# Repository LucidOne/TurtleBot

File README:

I Heart Engineering Documentation and Tools for the TurtleBot

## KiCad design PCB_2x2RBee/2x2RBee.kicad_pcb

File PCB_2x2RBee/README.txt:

2x2RBee
GPIO Control for the Raspberry Pi with XBee Shield included

BOM
Qty.	Item					Digikey P. No.		Manufacturer		Manufacturer P. No.	url
----------------------------------------------------------------------------------------------------------------------------------	

5	CONN TERM BLOCK 2.54MM 2POS PCB		ED10561-ND		On Shore Technology Inc	OSTVN02A150		http://www.on-shore.com/sites/default/files/manuals/ostvnxxa150.pdf

1	CONN JACK POWER 2.1MM PCB		CP-102A-ND		CUI Inc			PJ-102A			http://www.cui.com/Product/Resource/DigiKeyPDF/PJ-102A.pdf

1	CONN HEADR FMALE 26POS .1" DL AU	S9198-ND	Sullins Connector Solutions	SFH11-PBPC-D13-ST-BK	http://media.digikey.com/pdf/Data%20Sheets/Sullins%20PDFs/SFH11-PxxC-Dxx-ST-xx%2011160-C.pdf

1	CONN RCPT REV MICRO USB TYPE B		609-4048-1-ND		FCI			10103592-0001LF		http://portal.fciconnect.com/Comergent//fci/drawing/10103592.pdf

2	RELAY GENERAL PURPOSE SPST 3A 5V	PCN-105D3MHZ 000-ND 	TE Connectivity		PCN-105D3MHZ,000	http://www.te.com/commerce/DocumentDelivery/DDEController?Action=srchrtrv&DocNm=1461491&DocType=Customer+Drawing&DocLang=English

1	PHOTOCOUPLER DUAL 6N136 8-DIP		TLP2531F-ND		Toshiba			TLP2531(F)		http://www.semicon.toshiba.co.jp/info/docget.jsp?type=datasheet&lang=en&pid=TLP2530

2	IC SGL SCHMT-TRIG INVERT SC70-5		296-11608-1-ND		Texas Instruments	SN74LVC1G14DCKR		http://www.ti.com/lit/ds/symlink/sn74lvc1g14.pdf

2	IC REG LDO 5V .15A SOT23-5		296-20717-1-ND		Texas Instruments	LP2985-50DBVT		http://www.ti.com/lit/ds/symlink/lp2985-18.pdf

5	1K Resistor				P1.00KCTR-ND		Panasonic - ECG		ERJ-6ENF1001V	http://industrial.panasonic.com/www-data/pdf/AOA0000/AOA0000PE3.pdf

2 	RES 680 OHM 1/8W 1% 0805 SMD		311-680CRTR-ND		Yageo			RC0805FR-07680RL	http://www.yageo.com/documents/recent/PYu-RC0805_51_RoHS_L_4.pdf	

1	SWITCH SLIDE SPDT 30V.2A PC MNT		EG1903-ND		E-Switch			EG1218		http://spec.e-switch.com/P-J/P040040c.pdf

3	LED_0805				754-1131-2-ND		Kingbright Corp		APT2012SGC	http://www.us.kingbright.com/images/catalog/SPEC/APT2012SGC.pdf

1	FUSE PTC RESET 2.0A 6V 1206 SMD			F4155CT-ND		Littelfuse Inc		1206L200PR		http://www.littelfuse.com/~/media/Files/Littelfuse/Technical%20Resources/Documents/Data%20Sheets/Littelfuse_PTC_1206L.pdf

1	DIODE SCHOTTKY 40V 2A 1206			478-7806-1-ND		AVX Corporation		SD1206S040S2R0		http://www.avx.com/docs/Catalogs/schottky.pdf

2 	CONN SOCKET 10POS 2MM VERT T/H		3M9405-ND		3M		950510-6102-AR		http://multimedia.3m.com/mws/mediawebserver?66666UuZjcFSLXTtmXMEm8TaEVuQEcuZgVs6EVs6E666666--

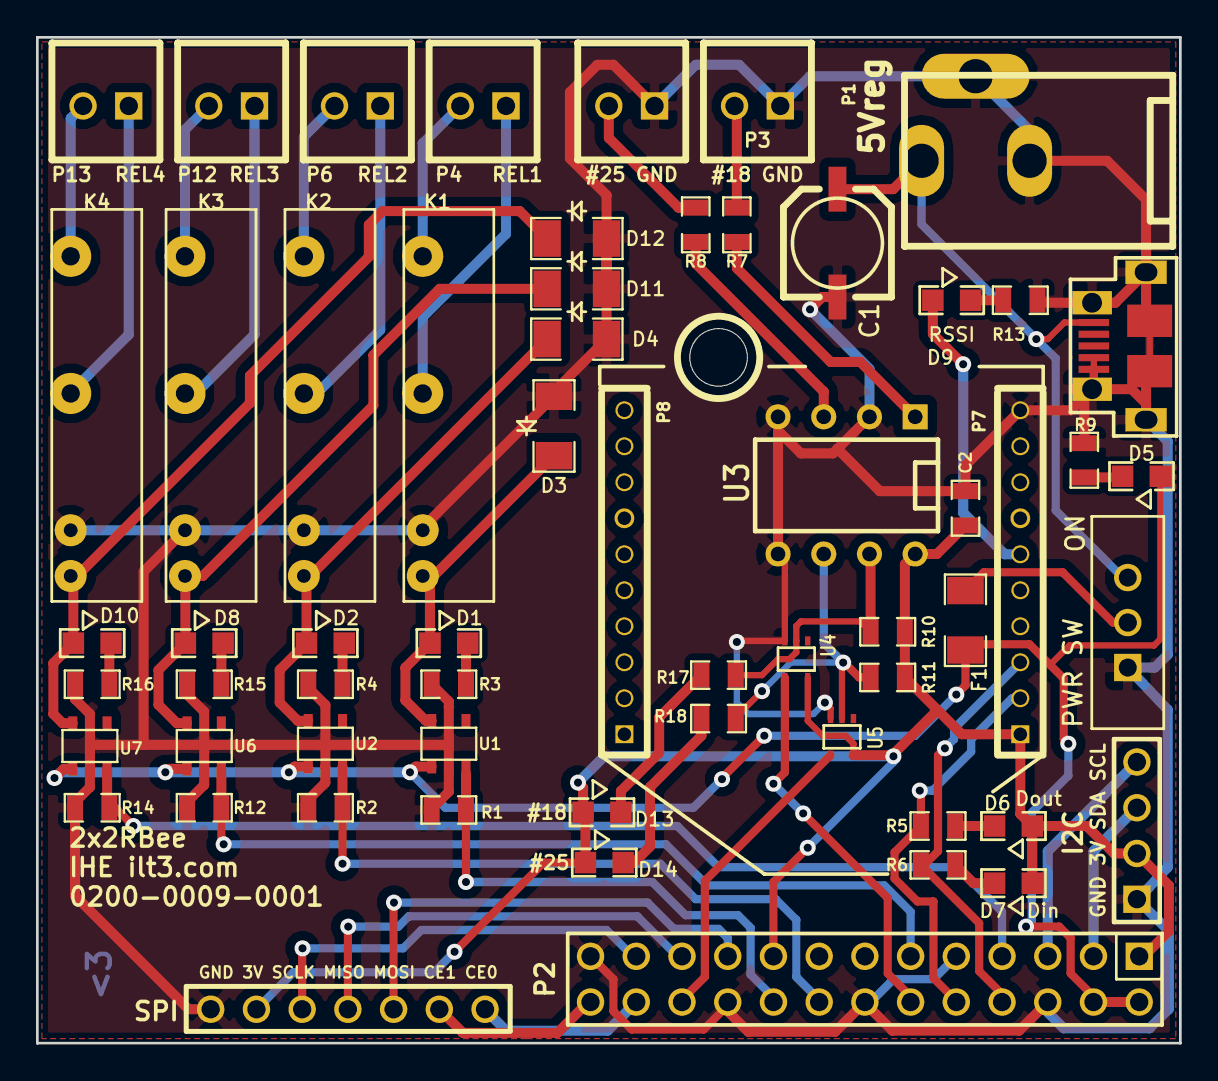
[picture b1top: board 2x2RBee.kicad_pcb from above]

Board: 2 copper layers, 63.5 x 55.9 mm, 60 parts (0 on the bottom side), 48 nets.

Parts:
1PIN: P***; 1pin_NPTH_Mechanical_M3_Screw
C1: 10uF; SMD_CAP_5m
C2: 0.1uF; SM0805_NonPol
D1, D2, D5, D8, D10, D13, D14: LED; LED_SMD_0805
D3, D4, D11, D12: DIODE; SM1206_diode
D6: Dout; LED_SMD_0805
D7: Din; LED_SMD_0805
D9: RSSI; LED_SMD_0805
F1: FUSE; SM1206
K1, K2, K3, K4: RELAY; Relay
P1: 5Vreg; PJ-102A
P2: CONN_13X2; pin_array_13x2
P3: IN_18; PIN_ARRAY_2X1_Screw Terminal
P4: REL1; PIN_ARRAY_2X1_Screw Terminal
P6: REL2; PIN_ARRAY_2X1_Screw Terminal
P7, P8: CONN_10; pin_array_10x1,2mm
P9: SPI; pin_array_7x1
P10: I2C; PIN_ARRAY_4x1
P12: REL3; PIN_ARRAY_2X1_Screw Terminal
P13: REL4; PIN_ARRAY_2X1_Screw Terminal
PWR1: USB; USB_micro-female
R1, R2, R3, R4, R5, R6, R9, R10, R11, R12, R13, R14, R15, R16, R17, R18: 1k; SM0805_NonPol
R7, R8: 680; SM0805_NonPol
SW1: PWR SW; SW_Slide_6x2mm
U1, U2, U6, U7: LowCurVReg; SOT23-5
U3: TLP2531; DIP-8__300
U4, U5: INVERTER-1CH; SOT353

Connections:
/3V3: C2.1, D6.1, D7.1, D13.1, D14.1, P2.1, P2.17, P7.1, P9.2, P10.2, R10.2, R11.2, U3.8, U4.5, U5.5
/5V-RPI: D5.1, F1.2, P2.2, P2.4, U1.1, U2.1, U6.1, U7.1
/5V-Relay1: D1.1, D3.2, K1.1, U1.5
/5V-Relay2: D2.1, D4.2, K2.1, U2.5
/5V-Relay3: D8.1, D11.2, K3.1, U6.5
/5V-Relay4: D10.1, D12.2, K4.1, U7.5
/5Vreg: C1.1, P1.1, PWR1.1, SW1.3
/CE0: P2.24, P9.7
/CE1: P2.26, P9.6
/Din: P2.8, P7.3, R6.1
/Dout: P2.10, P7.2, R5.1
/GPIO_4: P2.7, R14.2, U7.3
/GPIO_17: P2.11, R12.2, U6.3
/GPIO_18: P2.12, U4.4
/GPIO_23: P2.16, R2.2, U2.3
/GPIO_24: P2.18, R1.2, U1.3
/GPIO_25: P2.22, U5.4
/IN_18: P3.2, R7.1
/MISO: P2.21, P9.4
/MOSI: P2.19, P9.5
/RSSI: D9.1, P7.6
/SCL: P2.5, P10.4
/SCLK: P2.23, P9.3
/SDA: P2.3, P10.3
GND: C1.2, C2.2, D3.1, D4.1, D11.1, D12.1, K1.2, K2.2, K3.2, K4.2, P1.2, P1.3, P2.6, P2.9, P2.14, P2.20, P2.25, P3.1, P7.10, P9.1, P10.1, PWR1.4, PWR1.5, PWR1.6, R1.1, R2.1, R3.1, R4.1, R9.1, R12.1, R13.1, R14.1, R15.1, R16.1, SW1.1, U1.2, U2.2, U3.2, U3.4, U3.5, U4.3, U5.3, U6.2, U7.2
unnamed: D14.2, R18.2
unnamed: D13.2, R17.2
unnamed: D9.2, R13.2
unnamed: D7.2, R6.2
unnamed: D6.2, R5.2
unnamed: K4.4, P13.2
unnamed: K4.3, P13.1
unnamed: K3.4, P12.2
unnamed: K3.3, P12.1
unnamed: D10.2, R16.2
unnamed: D8.2, R15.2
unnamed: R11.1, R18.1, U3.6, U5.2
unnamed: K1.4, P4.2
unnamed: K1.3, P4.1
unnamed: K2.4, P6.2
unnamed: K2.3, P6.1
unnamed: R10.1, R17.1, U3.7, U4.2
unnamed: R8.2, U3.3
unnamed: R7.2, U3.1
unnamed: F1.1, SW1.2
unnamed: D5.2, R9.2
unnamed: D2.2, R4.2
unnamed: D1.2, R3.2

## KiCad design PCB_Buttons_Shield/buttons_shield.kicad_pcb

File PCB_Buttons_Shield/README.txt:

Arduino Buttons Shield for TurtleBot
0200-0003-0001

Included:
- Bill of Materials *
- Schematic
- KiCad board file
- Gerber files

* coming soon

BOM

Item					Digikey P. No.		Manufacturer		Manufacturer P. No.	URL
--------------------------------------------------------------------------------------------------------------------------------------------
TERM BLOCK 8POS SIDE ENT 2.54MM		A98338-ND		TE Connectivity		282834-8	http://documents.tycoelectronics.com/commerce/DocumentDelivery/DDEController?Action=srchrtrv&DocNm=282834&DocType=CD&DocLang=EN

SWITCH TACTILE SPST-NO 0.05A 12V	679-2401-ND		APEM Components, LLC	MJTP1119	http://www.apem.com/pdf/MJTP_6MM.pdf

CONN HDR BRKWAY .100 80POS VERT		A34976-40-ND		TE Connectivity		9-146254-0	http://documents.tycoelectronics.com/commerce/DocumentDelivery/DDEController?Action=srchrtrv&DocNm=146254&DocType=CD&DocLang=EN

CONN TERM BLOCK SPRNG 8POS 2.5MM	277-1800-ND			Phoenix Contact			1990067		http://www.phoenixcontact.com/online/portal/us/pxc/product_detail_page/!ut/p/b1/04_SjzQ0tTQ2MTMzM7TQj9CPykssy0xPLMnMz0vMAfGjzOJDnEJcXQOMzAz9A02dDDxdTJ1dfUyCDD38jIAKIvEocDQkTr8BDuBoQEh_uH4UXiUgF4AV4LHCzyM_N1U_NyrHzdJT1xEAasn7vg!!/dl4/d5/L0lDU0lKSmdrS0NsRUp

CONN SOCKET IDC 4POS DL SR 30AU		71600-004LF-ND		FCI			71600-004LF	http://portal.fciconnect.com/Comergent//fci/drawing/71600.pdf

SWITCH PUSH DPST-NC 0.1A 25V		1.15154.0060301-ND	C&K Components		1.15154.0060301	http://www.ck-components.com/index.php?module=media&action=Display&cmpref=43166&lang=en&width=&height=&format=&alt=

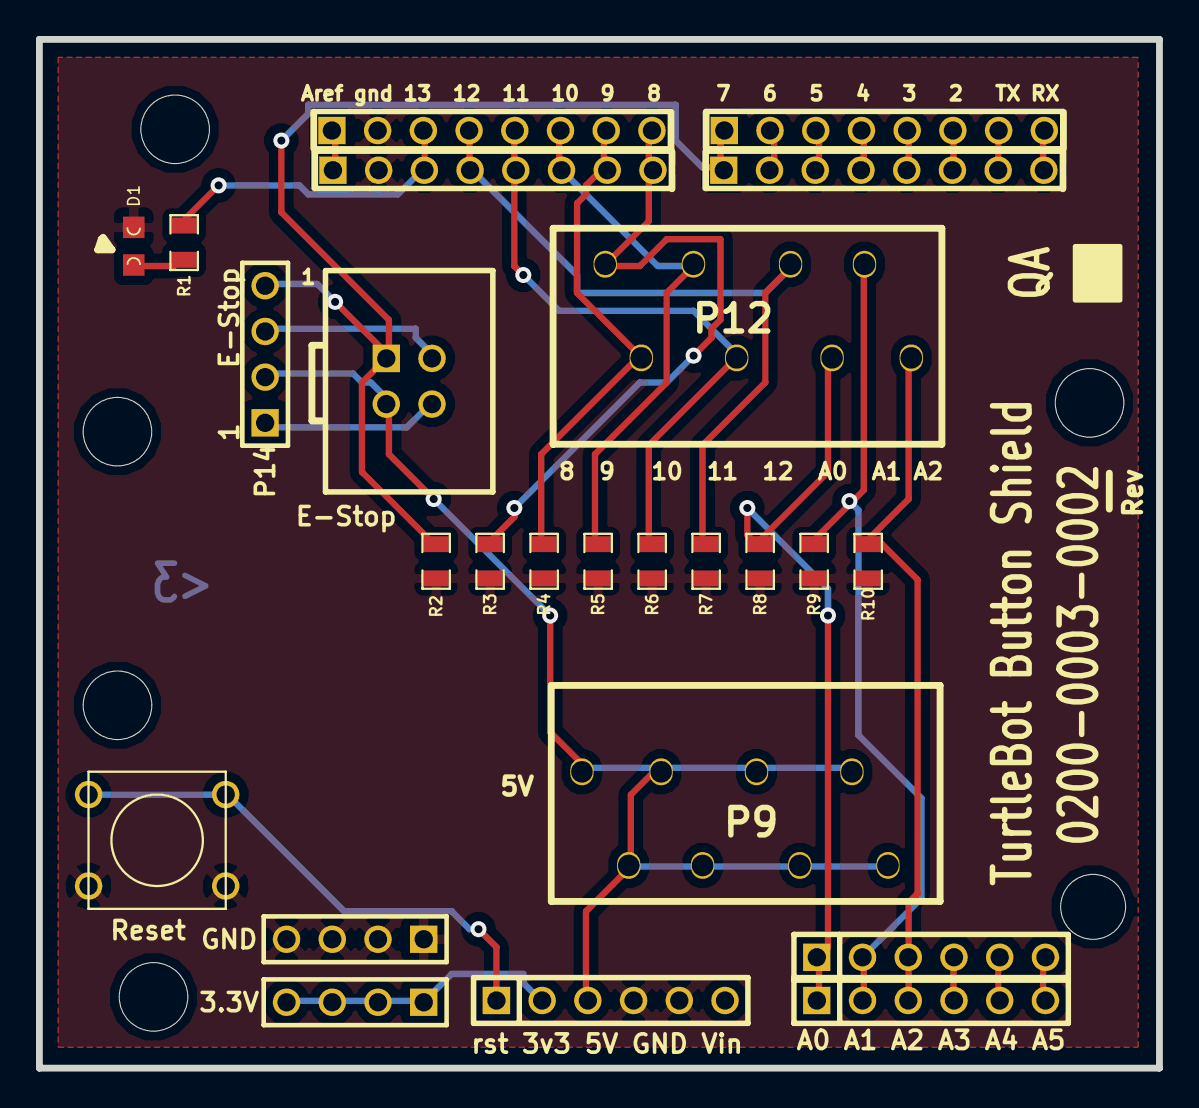
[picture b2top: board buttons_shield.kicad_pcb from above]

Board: 2 copper layers, 62.2 x 57.2 mm, 25 parts (0 on the bottom side), 28 nets.

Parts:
A0 A1 A2 A3 A4 A5: CONN_6; PIN_ARRAY-6X1
D1: LED; LED-0805
P2: CONN_6; PIN_ARRAY-6X1
P4: Aref gnd 13 12 11 10 9 8; pin_array_8x1
P5, P7: CONN_8; pin_array_8x1
P6: 7 6 5 4 3 2 TX RX; pin_array_8x1
P9: 5V; Term Block 8pin Snap Conn
P10: GND; PIN_ARRAY_4x1
P11: E-Stop; PIN_ARRAY_2X2
P12: 8 9 10 11 12 A0 A1 A2; Term Block 8pin Snap Conn
P13: 3.3V; PIN_ARRAY_4x1
P14: 1 E-Stop; PIN_ARRAY_4x1
R1, R2, R3, R4, R5, R6, R7, R8, R9, R10: R; SM0805_NonPol
SW1: Reset; SW_PUSH_SMALL
rst 3v3 5V GND Vin: CONN_6; PIN_ARRAY-6X1

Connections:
/2: P5.6, P6.6
/3: P5.5, P6.5
/3.3V: P13.1, P13.2, P13.3, P13.4, rst 3v3 5V GND Vin.2
/4: P5.4, P6.4
/5: P5.3, P6.3
/5V: P9.1, P9.2, P9.3, P9.4, P9.5, P9.6, P9.7, P9.8, P11.3, P14.2, rst 3v3 5V GND Vin.3
/6: P5.2, P6.2
/7: P5.1, P6.1, P11.1, P14.4, R2.1
/8: P4.8, P7.8, P12.1, R3.2
/9: P4.7, P7.7, P12.2, R4.2
/10: P4.6, P7.6, P12.3, R5.2
/11: P4.5, P7.5, P12.4, R6.2
/12: P4.4, P7.4, P12.5, R7.2
/13: P4.3, P7.3, R1.2
/A0: A0 A1 A2 A3 A4 A5.1, P2.1, P12.6, R8.2
/A1: A0 A1 A2 A3 A4 A5.2, P2.2, P12.7, R9.2
/A2: A0 A1 A2 A3 A4 A5.3, P2.3, P12.8, R10.2
/A3: A0 A1 A2 A3 A4 A5.4, P2.4
/A4: A0 A1 A2 A3 A4 A5.5, P2.5
/A5: A0 A1 A2 A3 A4 A5.6, P2.6
/AREF: P4.1, P7.1
/RESET: SW1.1, rst 3v3 5V GND Vin.1
/RX: P5.8, P6.8
/TX: P5.7, P6.7
GND: D1.2, P4.2, P7.2, P10.1, P10.2, P10.3, P10.4, R2.2, R3.1, R4.1, R5.1, R6.1, R7.1, R8.1, R9.1, R10.1, SW1.2, rst 3v3 5V GND Vin.4, rst 3v3 5V GND Vin.5
unnamed: P11.2, P14.3
unnamed: P11.4, P14.1
unnamed: D1.1, R1.1

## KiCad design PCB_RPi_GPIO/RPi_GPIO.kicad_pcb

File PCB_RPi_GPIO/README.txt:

RPi GPIO

BOM
Qty.	Item					Digikey P. No.		Manufacturer		Manufacturer P. No.	url
----------------------------------------------------------------------------------------------------------------------------------	

5	TERM BLOCK 2POS SIDE ENT 2.54MM		A98333-ND		TE Connectivity 	282834-2

1	CONN HEADR FMALE 26POS .1" DL AU	S9198-ND	Sullins Connector Solutions	SFH11-PBPC-D13-ST-BK	http://media.digikey.com/pdf/Data%20Sheets/Sullins%20PDFs/SFH11-PxxC-Dxx-ST-xx%2011160-C.pdf

2	RELAY GENERAL PURPOSE SPST 3A 5V	PCN-105D3MHZ 000-ND TE Connectivity	PCN-105D3MHZ,000	http://www.te.com/commerce/DocumentDelivery/DDEController?Action=srchrtrv&DocNm=1461491&DocType=Customer+Drawing&DocLang=English

1 	IC REG LDO 5V 1.5A D2PAK-3 		296-20796-1-ND		Texas Instruments	UA7805CKTTR		http://www.ti.com/lit/ds/symlink/ua7805.pdf

1	PHOTOCOUPLER DUAL 6N136 8-DIP		TLP2531F-ND		Toshiba			TLP2531(F)		http://www.semicon.toshiba.co.jp/info/docget.jsp?type=datasheet&lang=en&pid=TLP2530

1	IC INVERTER DUAL UNBUFFER 6TSSOP	568-9236-1-ND		NXP Semiconductors	74HC2GU04GW,125		http://www.nxp.com/documents/data_sheet/74HC2GU04.pdf

2	IC REG LDO 5V .15A SOT23-5		296-20717-1-ND		Texas Instruments	LP2985-50DBVT		http://www.ti.com/lit/ds/symlink/lp2985-18.pdf

2	1K Resistor				P1.00KCTR-ND		Panasonic - ECG		ERJ-6ENF1001V	http://industrial.panasonic.com/www-data/pdf/AOA0000/AOA0000PE3.pdf

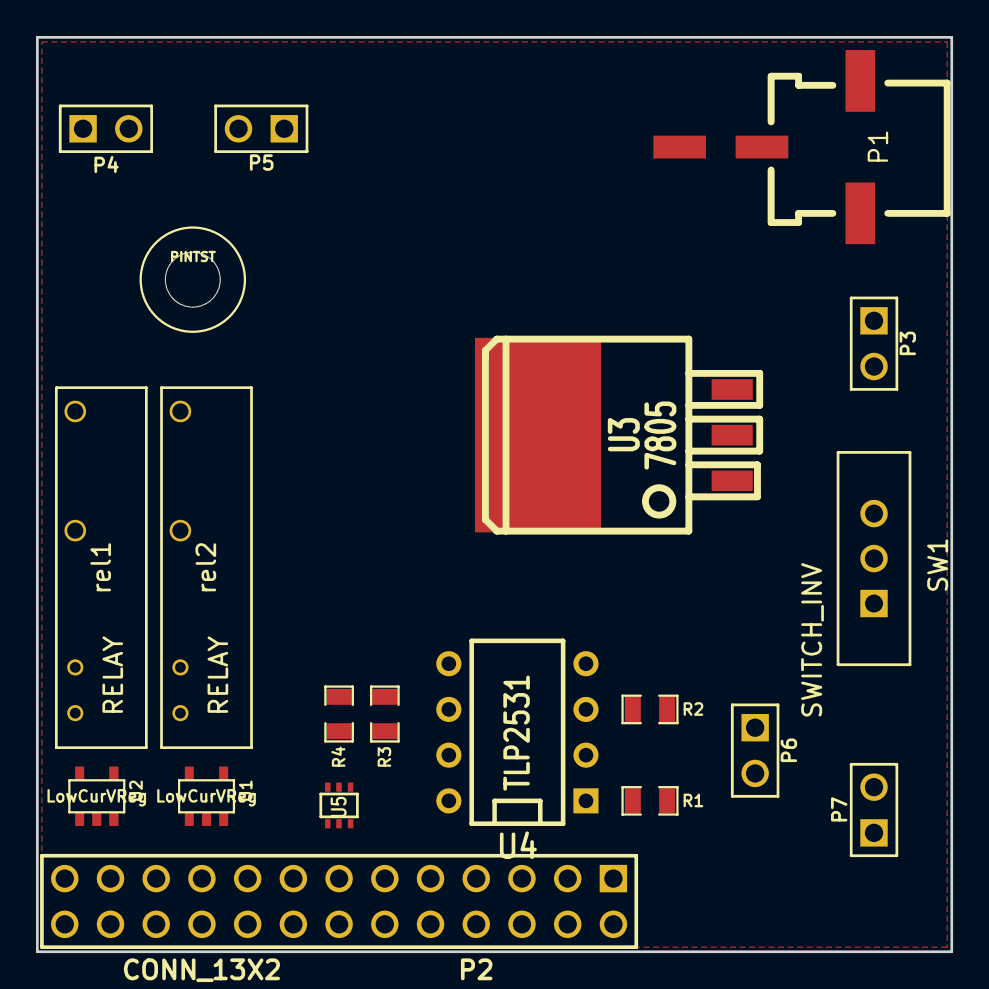
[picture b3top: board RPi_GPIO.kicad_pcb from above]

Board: 2 copper layers, 50.8 x 50.8 mm, 20 parts (0 on the bottom side), 20 nets, no tracks yet.

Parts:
P1: VIN; SMD Microfit 2pin
P2: CONN_13X2; pin_array_13x2
P3: VIN; PIN_ARRAY_2X1
P4: REL1; PIN_ARRAY_2X1
P5: REL2; PIN_ARRAY_2X1
P6: INPUT; PIN_ARRAY_2X1
P7: 5V; PIN_ARRAY_2X1
PINTST: Val*; PINTST
R1, R2: 680; SM0805_NonPol
R3, R4: R; SM0805_NonPol
SW1: SWITCH_INV; SW_Slide_6x2mm
U1, U2: LowCurVReg; SOT23-5
U3: 7805; TO263
U4: TLP2531; DIP-8__300
U5: INVERTER-2CH; SOT363
rel1, rel2: RELAY; Relay

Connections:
/3V3: P2.1, R3.2, R4.2, U4.8, U5.5
/5V-RPI: P2.2, P2.4, P7.1, U3.3
/5V-Relay1: U1.5, U2.5, rel1.1, rel2.1
/12V: SW1.2, U1.1, U2.1, U3.1
/GPIO_18: P2.12, U5.6
/GPIO_23: P2.16, U1.3
/GPIO_24: P2.18, U2.3
/GPIO_25: P2.22, U5.4
/IN_18: P6.2, R1.1
/IN_25: P6.1, R2.1
/V_IN: P1.1, P3.1, SW1.3
GND: P1.2, P2.6, P2.9, P2.14, P2.20, P2.25, P3.2, P7.2, SW1.1, U1.2, U2.2, U3.2, U4.2, U4.4, U4.5, U5.2, rel1.2, rel2.2
unnamed: P5.1, rel2.3
unnamed: P5.2, rel2.4
unnamed: R1.2, U4.1
unnamed: R2.2, U4.3
unnamed: P4.1, rel1.3
unnamed: P4.2, rel1.4
unnamed: R4.1, U4.6, U5.3
unnamed: R3.1, U4.7, U5.1

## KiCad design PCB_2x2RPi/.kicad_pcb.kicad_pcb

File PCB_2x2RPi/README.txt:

2x2RPi
GPIO Control for the Raspberry Pi

BOM
Qty.	Item					Digikey P. No.		Manufacturer		Manufacturer P. No.	url
----------------------------------------------------------------------------------------------------------------------------------	

5	CONN TERM BLOCK 2.54MM 2POS PCB		ED10561-ND		On Shore Technology Inc	OSTVN02A150		http://www.on-shore.com/sites/default/files/manuals/ostvnxxa150.pdf

1	CONN JACK POWER 2.1MM PCB		CP-102A-ND		CUI Inc			PJ-102A			http://www.cui.com/Product/Resource/DigiKeyPDF/PJ-102A.pdf

1	CONN HEADR FMALE 26POS .1" DL AU	S9198-ND	Sullins Connector Solutions	SFH11-PBPC-D13-ST-BK	http://media.digikey.com/pdf/Data%20Sheets/Sullins%20PDFs/SFH11-PxxC-Dxx-ST-xx%2011160-C.pdf

1	CONN RCPT REV MICRO USB TYPE B		609-4048-1-ND		FCI			10103592-0001LF		http://portal.fciconnect.com/Comergent//fci/drawing/10103592.pdf

2	RELAY GENERAL PURPOSE SPST 3A 5V	PCN-105D3MHZ 000-ND 	TE Connectivity		PCN-105D3MHZ,000	http://www.te.com/commerce/DocumentDelivery/DDEController?Action=srchrtrv&DocNm=1461491&DocType=Customer+Drawing&DocLang=English

1	PHOTOCOUPLER DUAL 6N136 8-DIP		TLP2531F-ND		Toshiba			TLP2531(F)		http://www.semicon.toshiba.co.jp/info/docget.jsp?type=datasheet&lang=en&pid=TLP2530

2	IC SGL SCHMT-TRIG INVERT SC70-5		296-11608-1-ND		Texas Instruments	SN74LVC1G14DCKR		http://www.ti.com/lit/ds/symlink/sn74lvc1g14.pdf

2	IC REG LDO 5V .15A SOT23-5		296-20717-1-ND		Texas Instruments	LP2985-50DBVT		http://www.ti.com/lit/ds/symlink/lp2985-18.pdf

5	1K Resistor				P1.00KCTR-ND		Panasonic - ECG		ERJ-6ENF1001V	http://industrial.panasonic.com/www-data/pdf/AOA0000/AOA0000PE3.pdf

2 	RES 680 OHM 1/8W 1% 0805 SMD		311-680CRTR-ND		Yageo			RC0805FR-07680RL	http://www.yageo.com/documents/recent/PYu-RC0805_51_RoHS_L_4.pdf	

1	SWITCH SLIDE SPDT 30V.2A PC MNT		EG1903-ND		E-Switch			EG1218		http://spec.e-switch.com/P-J/P040040c.pdf

3	LED_0805				754-1131-2-ND		Kingbright Corp		APT2012SGC	http://www.us.kingbright.com/images/catalog/SPEC/APT2012SGC.pdf

1	FUSE PTC RESET 2.0A 6V 1206 SMD			F4155CT-ND		Littelfuse Inc		1206L200PR		http://www.littelfuse.com/~/media/Files/Littelfuse/Technical%20Resources/Documents/Data%20Sheets/Littelfuse_PTC_1206L.pdf

1	DIODE SCHOTTKY 40V 2A 1206			478-7806-1-ND		AVX Corporation		SD1206S040S2R0		http://www.avx.com/docs/Catalogs/schottky.pdf

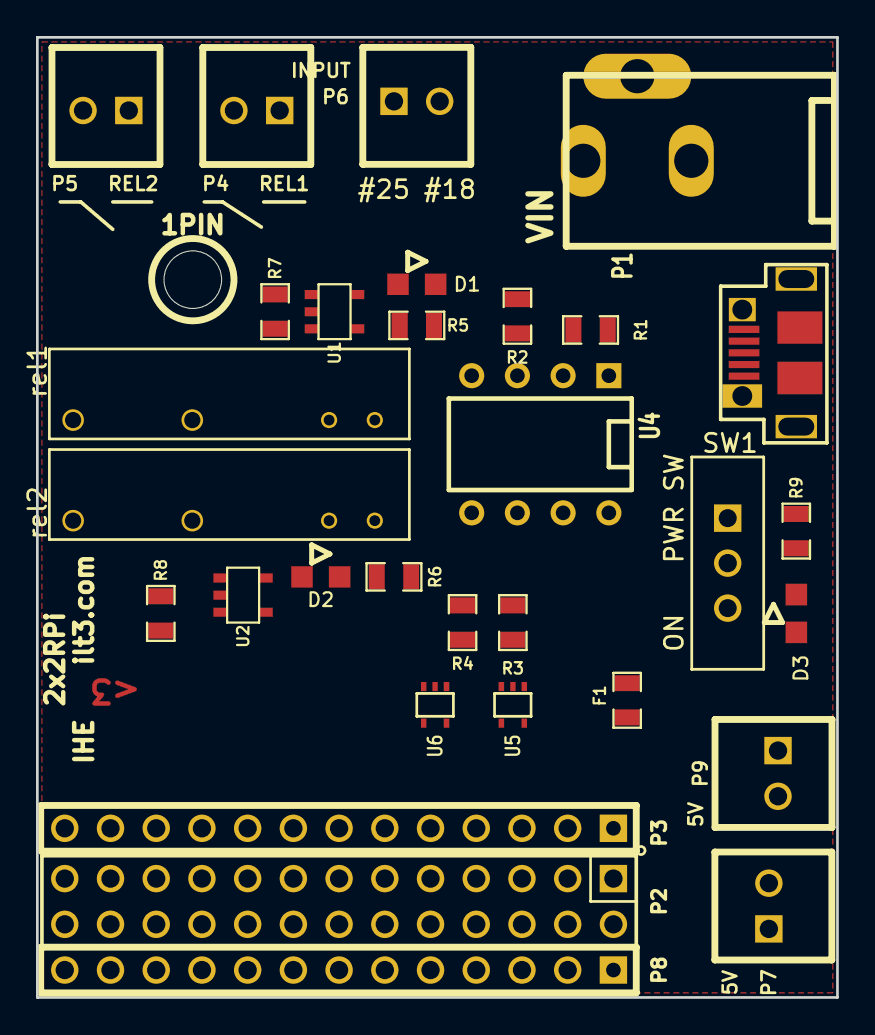
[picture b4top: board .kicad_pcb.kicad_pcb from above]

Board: 2 copper layers, 44.5 x 53.3 mm, 32 parts (0 on the bottom side), 40 nets, no tracks yet.

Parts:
1PIN: P***; 1pin_NPTH_Mechanical_M3_Screw
D1, D2, D3: DIODE; LED SMD 0805
F1: FUSE; SM0805_NonPol
J1: USB; USB micro-female
P1: VIN; PJ-102A
P2: CONN_13X2; pin_array_13x2
P3, P8: CONN_13; pin_array_13x1
P4: REL1; PIN_ARRAY_2X1_Screw Terminal
P5: REL2; PIN_ARRAY_2X1_Screw Terminal
P6: INPUT; PIN_ARRAY_2X1_Screw Terminal
P7, P9: 5V; PIN_ARRAY_2X1_Screw Terminal
R1, R2: 680; SM0805_NonPol
R3, R4, R7, R8, R9: 1k; SM0805_NonPol
R5, R6: R; SM0805_NonPol
SW1: PWR SW; SW_Slide_6x2mm
U1, U2: LowCurVReg; SOT23-5
U4: TLP2531; DIP-8__300
U5, U6: INVERTER-1CH; SOT353
rel1, rel2: RELAY; Relay

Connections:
/3V3: P2.1, P3.1, R3.2, R4.2, U4.8, U5.5, U6.5
/5V-RPI: D3.1, F1.2, P2.2, P2.4, P7.1, P8.1, P8.2, P9.2, U1.1, U2.1
/5V-Relay1: D1.1, U1.5
/5V-Relay2: D2.1, U2.5
/5Vreg: J1.1, P1.1, SW1.3
/GPIO_18: P2.12, P8.6, U5.4
/GPIO_23: P2.16, P8.8, R7.2, U1.3
/GPIO_24: P2.18, P8.9, R8.2, U2.3
/GPIO_25: P2.22, P8.11, U6.4
/IN_18: P6.2, R1.1
/IN_25: P6.1, R2.1
GND: J1.4, J1.5, J1.6, P1.2, P2.6, P2.9, P2.14, P2.20, P2.25, P3.5, P3.13, P7.2, P8.3, P8.7, P8.10, P9.1, R7.1, R8.1, R9.1, SW1.1, U1.2, U2.2, U4.2, U4.4, U4.5, U5.3, U6.3, rel1.2, rel2.2
unnamed: D1.2, R5.1
unnamed: R6.2, rel2.1
unnamed: D3.2, R9.2
unnamed: F1.1, SW1.2
unnamed: D2.2, R6.1
unnamed: R2.2, U4.3
unnamed: R1.2, U4.1
unnamed: R5.2, rel1.1
unnamed: P2.3, P3.2
unnamed: P2.10, P8.5
unnamed: P2.8, P8.4
unnamed: P2.26, P8.13
unnamed: P2.24, P8.12
unnamed: P2.21, P3.11
unnamed: P2.23, P3.12
unnamed: P2.19, P3.10
unnamed: P2.17, P3.9
unnamed: P2.15, P3.8
unnamed: P2.13, P3.7
unnamed: P2.11, P3.6
unnamed: P2.7, P3.4
unnamed: P2.5, P3.3
unnamed: R3.1, U4.7, U5.2
unnamed: R4.1, U4.6, U6.2
unnamed: P4.2, rel1.4
unnamed: P4.1, rel1.3
unnamed: P5.2, rel2.4
unnamed: P5.1, rel2.3

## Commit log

2011-07-13 Now available for public consumption
2011-07-13 removing extra lock
2012-01-23 UCK Customization scripts for ROS ISO Generator
2012-01-23 Added initial version of PCB files for power splitter
2012-01-23 added gerbers
2012-01-31 Added Power Splitter Board and Schematic files
2012-02-01 Added Bill of Materials
2012-02-01 Fixed file versions
2012-02-01 Added Gerber Files
2012-02-01 Updated list of gerber files
2012-02-06 Updated drill file
2012-02-06 Fixed drill file and gerbers
2012-02-08 Fixed file names
2012-02-12 t push!
2012-02-27 fixed silk screen
2012-03-17 back silk screen fixed
2012-03-26 ROFL project added
    Ring Of Fire Light added to turtlebot projects
2012-03-26 Added README file
2012-03-26 Added board file
2012-03-28 Updated board modules
2012-03-29 Organized components
2012-03-30 Updated Arduino Pro size
2012-04-04 Layout Draft 1
2012-04-08 Fixing Layout
2012-04-09 Realigned LEDs
2012-04-10 Updated BOM, Added Board-to-Board connectors
2012-04-10 Gerber Files generated (first draft)
2012-04-10 scora init commit
2012-04-16 Added Power Board EU version
2012-04-23 PCB_GYRO added
2012-04-24 Fixed gerber files (missing solder mask front)
2012-04-24 Organizded components PCB Gyro
    missing solder jumpers
2012-04-25 PCB Gyro gerber files done
2012-05-01 Fixed all connections on ROFL
2012-05-01 Added gerbers for fixed ROFL routing
2012-05-02 Generated Gerber files EU Power Supply
2012-05-06 Added Mini Fit Conn for Kinect
2012-05-07 Updated BOM for ROLF
2012-05-25 Added Buttons Arduino shield
2012-05-25 Updated Buttons Shield
2012-05-25 Generated Gerber files for buttons shield
2012-05-29 Created Gerber files for Buttons Shield
2012-05-31 Updated to Arduino Mega Shield
2012-06-04 rearranged European Power Board
2012-06-06 Added Snap conn Button Shield
2012-06-07 Finished Gerbers for Button Shield
2012-06-11 Updated Board file Button Shield
2012-06-11 Finished Rev1 SCORA and Power Board EU
2012-06-17 Power Board EU BOM added
2012-06-17 Del. Pricing
2012-06-18 Changed Folder Organization
2012-06-20 Added Pull down resistors Button Shield
2012-06-20 Added Gerbers Buttons Shield Rev2
2012-06-21 Added Maker Bot Hot plate files
2012-06-25 Fixed BOM for Power Interface Shield
2012-06-25 Added PDF Schematic for Power Interface Shield
2012-06-29 Initial Upload
2012-07-02 generated netlist
2012-07-02 Created missing footprints for components
2012-07-09 Hexagonal Footprint Added
2012-07-11 Upgrading Power Interface Shield
2012-07-14 Updated routing (incomplete - in progress)
2012-07-18 Added Orientation Sensor Board
2012-07-23 Added breakout pin for Power Interface Shield baud select
2012-07-24 Added Orientation Sensor Board files
2012-07-27 Routed LED'S colors together
2012-07-27 Complete Route
2012-07-27 Finalized V0x01 RGB HEXAlight
2012-07-30 Added Polar 9 IMU + Serial Numbers
2012-07-30 Changed Version Number
2012-07-30 Hotplate design progress
2012-07-31 Generated Gerber Files & Connected Interrupts to micrcontroller
2012-07-31 Connected Interrupts to microcontroller & added Gerber Fiiles
2012-08-01 Breakout for ATmega Controller
2012-08-03 Fixed BOM for Polar 9 IMU
2012-08-06 Fixed min drill hole values
2012-08-07 Added Power LED and Images of board layers
2012-08-13 Rev 2 of Power Interface Shield
2012-08-14 Organized folders and added Documentation Power Interface Shield
2012-08-15 Organized Subfolders, Fixed Power Interface Shield manual
2012-08-15 Cleaned RGB_HEXAlight files
2012-08-21 Added missing capacitors to Polar9IMU BOM
2012-08-21 Fixed USB micro pinout and added Rev 2 Power Interface Shield
2012-08-22 Added Buttons Shield User Manual
2012-09-01 Created Arduino Scripts. Updated BOM to include 12Ohm resistor
2012-09-04 Added Mating Connectors for Power Interface Shield
2012-09-10 Updated gerber files Polar 9 IMU
2012-09-11 Updated Rev 02 of Polar 9 IMU
2012-09-18 Finalized gerber files Rev 02 Polar 9 IMU, Added Battery Charger BOM
2012-10-04 Fixed Reset buttons pinout
2012-10-04 Fixed No Connect on V_in line
2012-10-09 Added diode and pull down resistor on Reset, R in parallel with crystal, and cap on AREF
2012-10-23 Added links for code examples Polar 9 IMU
2012-10-23 Polar 9 IMU Rev 02 - non-routed
2012-10-25 Fixed Gyro MISO and MOSI, Fixed Translator Pinout. Finished Gerbers
2012-10-30 Added ATMEGA328 template, drinks project
2012-11-06 Added BOM for ATMEGA328 Template
2012-11-08 Added correct part number for Atmega328P and cap cer 10uF
2012-11-14 Changed pin 10 to pin D10 ATMEGA328P
2012-11-14 Added Motor Controller updated files
2012-11-15 Added motor controller *needs tracks *gerbers coming soon
2012-11-21 Added LED Flash&Strip project
2012-11-27 Updatd Flash and Strip board and schematic
2012-12-13 Changed connectors Output Input BUS
2012-12-20 Updating tracks on strip board
2012-12-27 Added gerber files for Strip board of Flash&Strip
2012-12-28 Added gerber files for Flash board of Flash&Strip
2013-01-03 Made Strip board symmetric
2013-01-04 Added Gerbers for Flash&Strip Boards
2013-01-08 Deleted PCB_Drinks project (replaced by Flash&Strip project), added BOM and gerbers for Flash&Strip
2013-01-08 Cleaned unnecessary backup files, deleted ROFL files
2013-01-30 Added RPi GPIO project
2013-02-04 Changed RPi_GPIO to 2x2RPi, added gerbers
2013-02-04 2x2RPi gerbers ready for manufacturing
2013-02-06 Added Power Switch to BOM
2013-02-25 Adding Motor Controller Arduino files (experimental)
2013-02-26 Working code with interrupts
2013-03-20 Motor control with pwm arduino sample code
2013-03-20 Adding target control using a second pot
2013-04-03 Adding kinect modification cable
2013-06-04 Adding new kicad file format for Buttons Shield
2013-06-13 Adding relay limiting resistor
2013-06-19 Updating button shield BOM
2013-06-19 Updating 2x2RPi not finished yet
2013-06-20 Adding new revisino 2x2RPi board
2013-06-20 2nd revision 2x2RPi board and gerber files, awaiting approval
2013-06-20 Adding sample button shield Arduino code
2013-06-24 Recreating schematic files, updating serial numbers
2013-06-26 Adding latest project gerbers
2013-06-26 Updated gerber files for 2x2Rpi
2013-06-26 Updated Strip gerber files for Flash and Strip project
2013-07-01 Adding sample code for motor controller using LMD18201
2013-07-02 Adding Strip copper layers gerber files
2013-07-02 Updating motor controller notes
2013-07-26 adding 2x2RBee files
2013-07-27 Adding schematic and gerber files for 2x2RBee board
